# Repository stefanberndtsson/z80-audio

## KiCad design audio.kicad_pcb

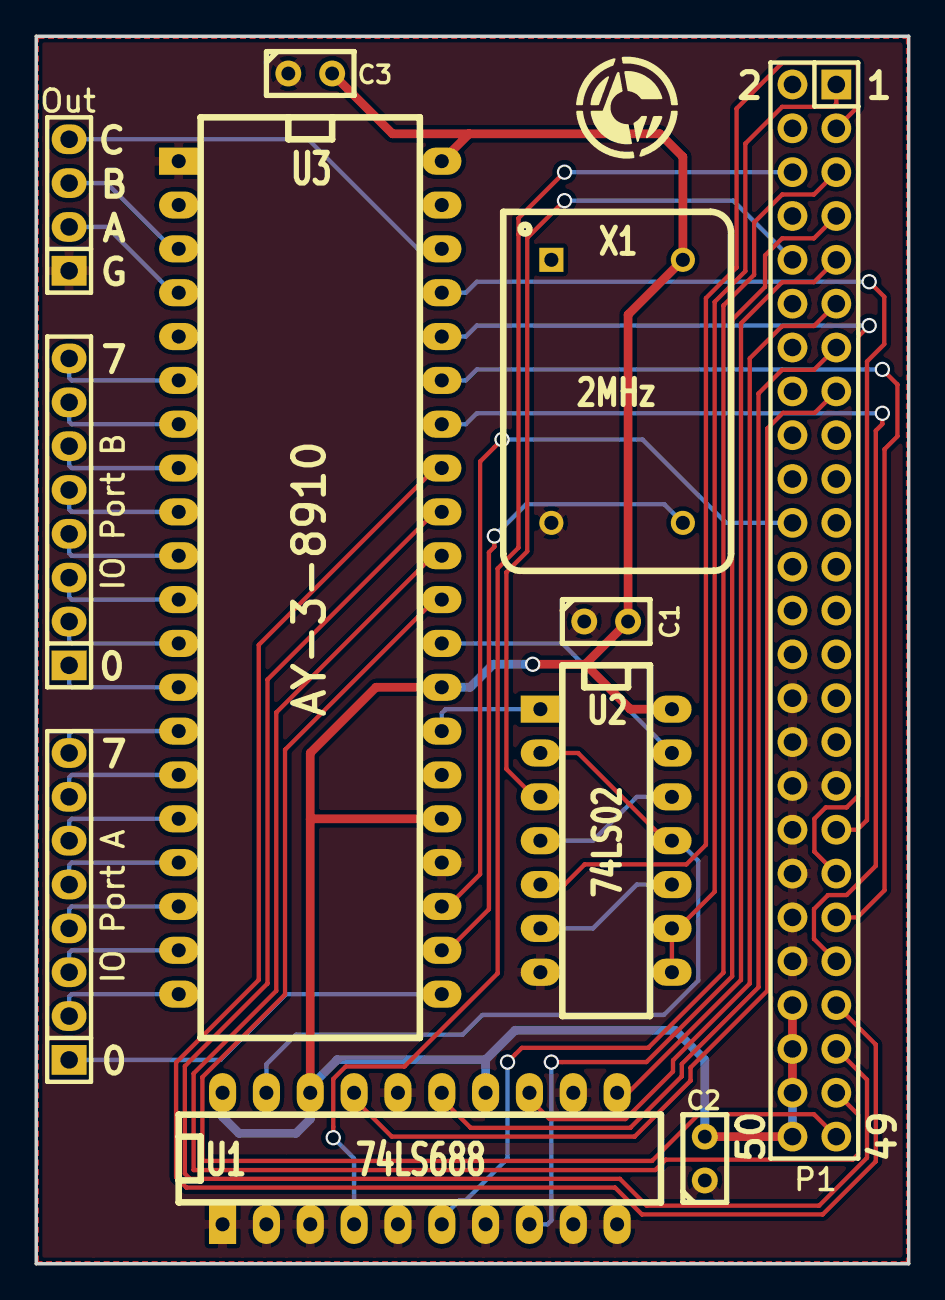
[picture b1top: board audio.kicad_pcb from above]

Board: 2 copper layers, 50.5 x 71.1 mm, 11 parts (0 on the bottom side), 46 nets.

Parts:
C1, C2, C3: C; Capacitor3MMDiscRM2.5
IO Port A: CONN_8; Socket_Strip_Straight_1x08
IO Port B: CONN_8; Socket_Strip_Straight_1x08
Out: CONN_4; Socket_Strip_Straight_1x04
P1: CONN_25X2; Socket_Strip_Straight_2x25
U1: 74LS688; DIP-20__300_ELL
U2: 74LS02; DIP-14__300_ELL
U3: AY-3-8910; DIP-40__600_ELL
X1: 2MHz; OSCILLATOR_KXO-200

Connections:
/A0: P1.1, U2.8, U2.9
/A1: P1.3, U2.5
/A2: P1.5, U1.6
/A3: P1.7, U1.8
/A4: P1.9, U1.11
/A5: P1.11, U1.13
/A6: P1.13, U1.15
/A7: P1.15, U1.17
/AYCLK: U3.22, X1.8
/AYCS: U1.19, U2.2, U2.11
/BC1: U2.13, U3.29
/BDIR: U2.1, U3.27
/CH_A: Out.2, U3.4
/CH_B: Out.3, U3.3
/CH_C: Out.4, U3.38
/D0: P1.35, U3.37
/D1: P1.37, U3.36
/D2: P1.39, U3.35
/D3: P1.41, U3.34
/D4: P1.43, U3.33
/D5: P1.45, U3.32
/D6: P1.47, U3.31
/D7: P1.49, U3.30
/IOA0: IO Port A.1, U3.21
/IOA1: IO Port A.2, U3.20
/IOA2: IO Port A.3, U3.19
/IOA3: IO Port A.4, U3.18
/IOA4: IO Port A.5, U3.17
/IOA5: IO Port A.6, U3.16
/IOA6: IO Port A.7, U3.15
/IOA7: IO Port A.8, U3.14
/IOB0: IO Port B.1, U3.13
/IOB1: IO Port B.2, U3.12
/IOB2: IO Port B.3, U3.11
/IOB3: IO Port B.4, U3.10
/IOB4: IO Port B.5, U3.9
/IOB5: IO Port B.6, U3.8
/IOB6: IO Port B.7, U3.7
/IOB7: IO Port B.8, U3.6
/IORQ: P1.6, U1.4
/RD: P1.10, U2.3
/RESET: P1.22, U3.23
GND: C1.1, C2.1, C3.1, Out.1, P1.30, P1.32, P1.33, P1.34, P1.36, P1.38, P1.40, P1.42, U1.1, U1.2, U1.3, U1.5, U1.7, U1.9, U1.10, U1.12, U1.16, U2.7, U3.1, U3.24, X1.7
unnamed: U2.6, U2.10
unnamed: U2.4, U2.12
VCC: C1.2, C2.2, C3.2, P1.44, P1.46, P1.48, P1.50, U1.14, U1.18, U1.20, U2.14, U3.25, U3.28, U3.40, X1.14

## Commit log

2014-08-15 Initial
